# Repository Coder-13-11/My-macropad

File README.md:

# Karthik's Macropad + Hack Club
My own macropad for my personal USE.

It has two layers to work with: one for media controls and the other for copy, paste, and undo. The knob click changes layers. It runs KMK, so it’s very easy to change it later if I want to add more functionality. There’s also an RGB LED, which I plan to use as a status LED. The OLED screen will have some animations and maybe some stats about my PC.

## Overview
3 macro buttons with 2 layers, Rotary encoder knob, 0.96" OLED display, 1 status RGB LED, XIAO RP2040 running KMK firmware

# Current status:
Waiting for Approval :D

## CAD Pictures
<p align="center">

_The PCB is PLACED in between the case parts  lol :)
</p>

## PCB

Schematic Design:

## BOM
1x Seeed XIAO RP2040
3x MX-switches
1x 0.91 inch OLED display
1x 3D-printed case
1x EC11 Rotary Encoder
4x M3 bolts and nuts
1x Custom PCB

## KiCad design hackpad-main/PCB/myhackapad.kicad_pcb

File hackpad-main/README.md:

# Karthik's Macropad + Hack Club
My own macropad for my personal USE.

It has two layers to work with: one for media controls and the other for copy, paste, and undo. The knob click changes layers. It runs KMK, so it’s very easy to change it later if I want to add more functionality. There’s also an RGB LED, which I plan to use as a status LED. The OLED screen will have some animations and maybe some stats about my PC.

## Overview
3 macro buttons with 2 layers, Rotary encoder knob, 0.96" OLED display, 1 status RGB LED, XIAO RP2040 running KMK firmware

# Current status:
Waiting for Approval :D

## CAD Pictures
<p align="center">

_The PCB is PLACED in between the case parts  lol :)
</p>

## BOM
1x Seeed XIAO RP2040
3x MX-switches
1x 0.91 inch OLED display
1x 3D-printed case
1x EC11 Rotary Encoder
4x M3 bolts and nuts
1x Custom PCB

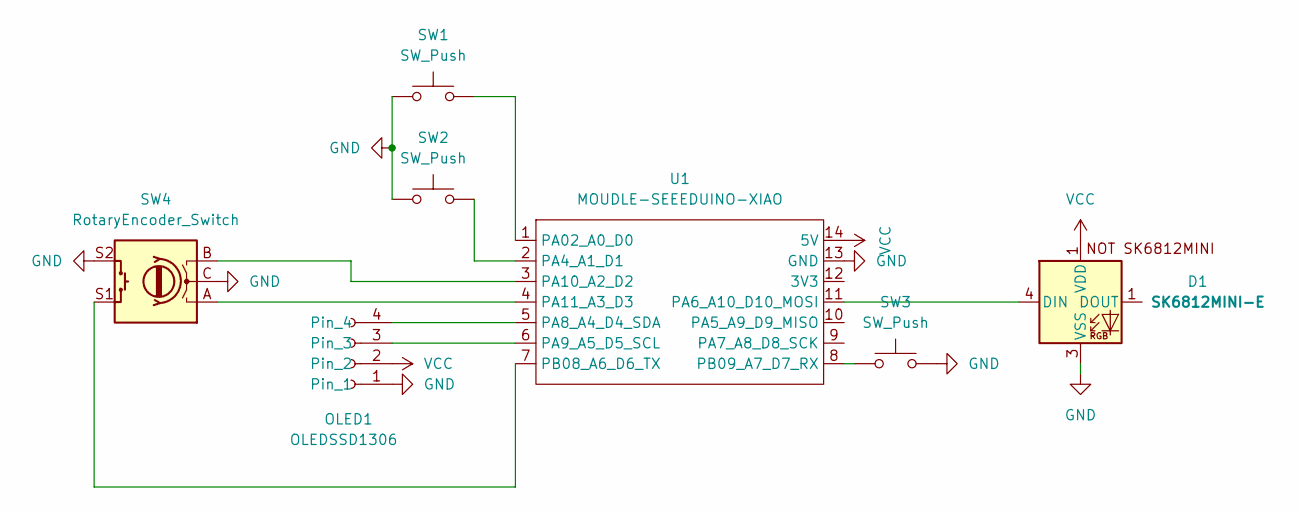
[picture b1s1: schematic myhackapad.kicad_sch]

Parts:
D1: SK6812MINI-E; SK6812MINI-E_fixed
OLED1: OLEDSSD1306; SSD1306-0.91-OLED-4pin-128x32
SW1, SW2, SW3: SW_Push; SW_Cherry_MX_1.00u_PCB
SW4: RotaryEncoder_Switch; RotaryEncoder_Alps_EC11E-Switch_Vertical_H20mm
U1: MOUDLE-SEEEDUINO-XIAO; XIAO-Generic-Hybrid-14P-2.54-21X17.8MM

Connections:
GND: D1.3 (VSS), OLED1.1, SW1.1, SW2.1, SW3.2, SW4.C, SW4.S2, U1.13 (GND)
unnamed: D1.4 (DIN), U1.11 (PA6_A10_D10_MOSI)
unnamed: OLED1.3, U1.6 (PA9_A5_D5_SCL)
unnamed: OLED1.4, U1.5 (PA8_A4_D4_SDA)
unnamed: SW1.2, U1.1 (PA02_A0_D0)
unnamed: SW2.2, U1.2 (PA4_A1_D1)
unnamed: SW4.B, U1.3 (PA10_A2_D2)
unnamed: SW4.A, U1.4 (PA11_A3_D3)
unnamed: SW4.S1, U1.7 (PB08_A6_D6_TX)
unnamed: SW3.1, U1.8 (PB09_A7_D7_RX)
VCC: D1.1 (VDD), OLED1.2, U1.14 (5V)

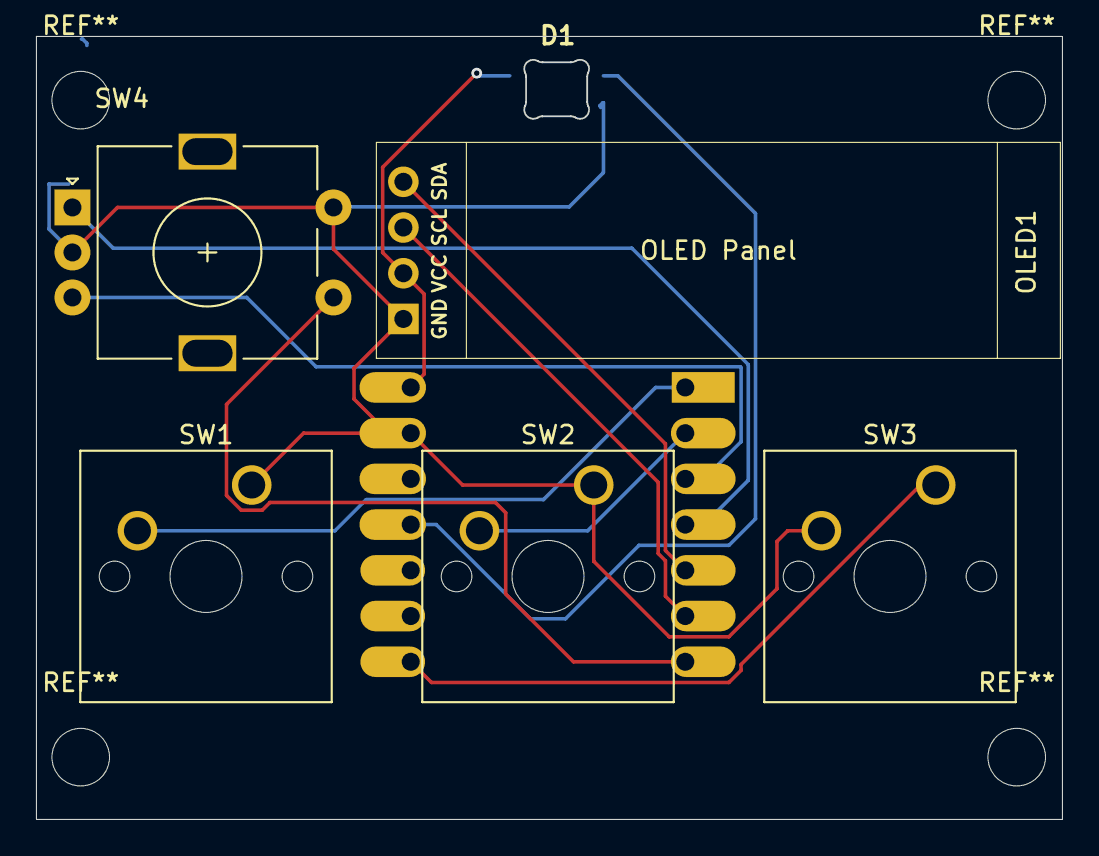
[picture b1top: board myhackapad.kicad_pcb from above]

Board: 2 copper layers, 56.9 x 43.5 mm, 7 parts (1 on the bottom side), 11 nets.

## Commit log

2026-06-18 Revise README for clarity and formatting
    Updated README to clarify usage and improve formatting.
2026-06-18 Update README to reflect new macropad owner
2026-06-18 Delete README.md content
    Removed the entire README content for the project.
2026-06-18 Revise README for Karthik's Macropad project
    Updated README to provide detailed information about Karthik's Macropad, including features, current status, CAD pictures, and bill of materials.
2026-06-18 Add PCB section with images to README
